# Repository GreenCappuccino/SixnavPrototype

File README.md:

# Shamrock Sixnav Prototype Board
This board is intended as a test platform for the development of an open-source knob
with 6 degrees of freedom (6DOF), based on the ideas expressed in expired US patent
[US20030102426A1](https://patents.google.com/patent/US20030102426A1).

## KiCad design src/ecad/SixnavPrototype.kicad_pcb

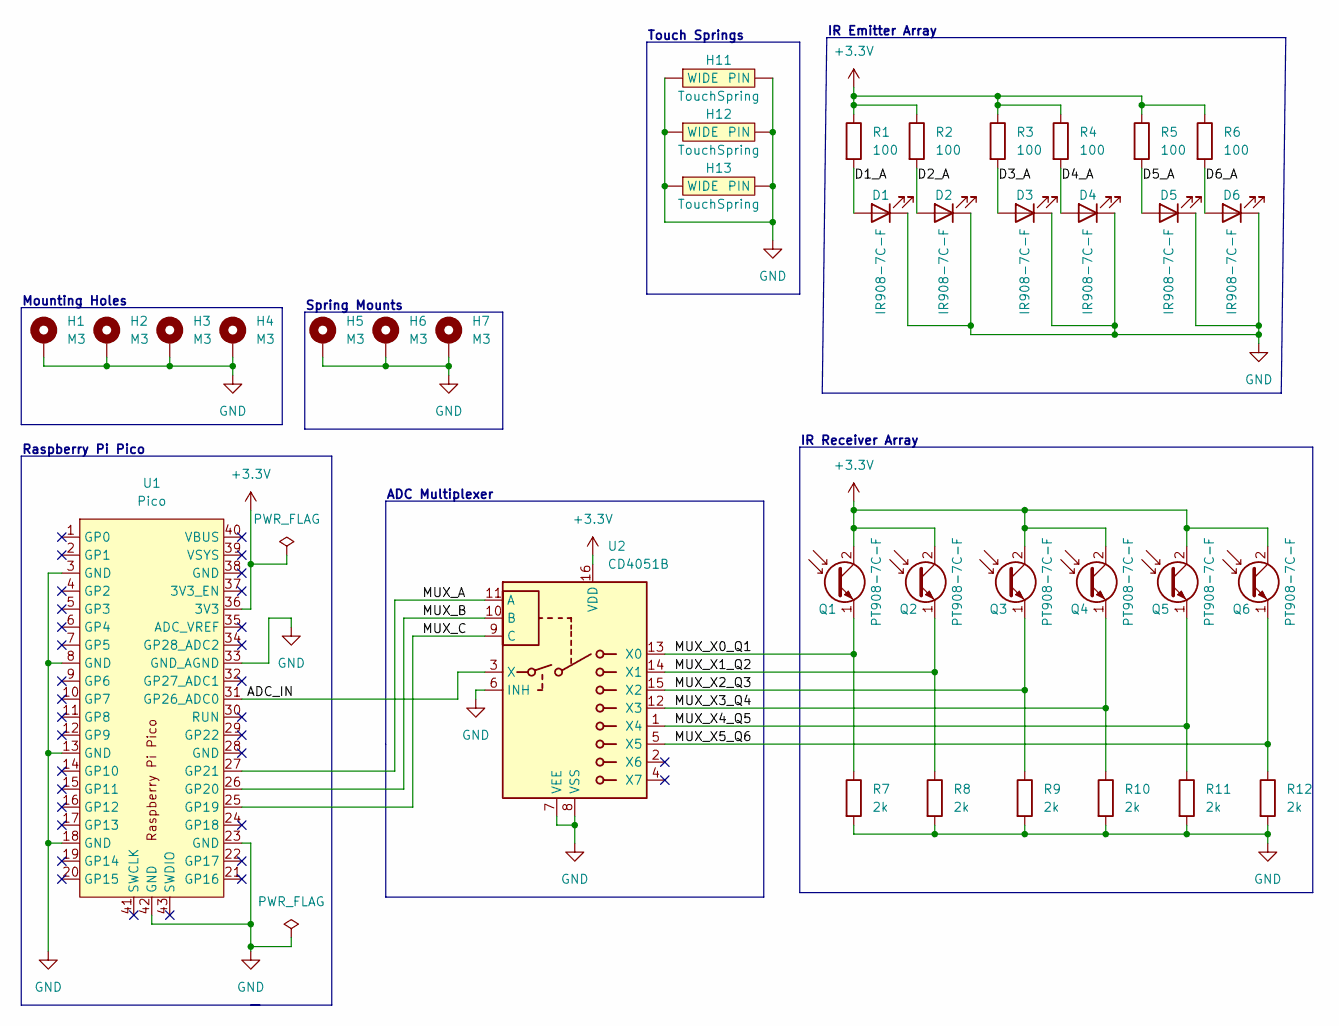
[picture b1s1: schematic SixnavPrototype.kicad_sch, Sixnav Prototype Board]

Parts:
D1, D2, D3, D4, D5, D6: IR908-7C-F
H1, H2, H3, H4, H5, H6, H7: M3; MountingHole_3.2mm_M3_DIN965_Pad
H11, H12, H13: TouchSpring; TouchSpring10mm
Q1, Q2, Q3, Q4, Q5, Q6: PT908-7C-F
R1, R2, R3, R4, R5, R6: 100; R_Axial_DIN0204_L3.6mm_D1.6mm_P5.08mm_Horizontal
R7, R8, R9, R10, R11, R12: 2k; R_Axial_DIN0204_L3.6mm_D1.6mm_P5.08mm_Horizontal
U1: Pico; Raspberry Pi Pico
U2: CD4051B; DIP-16_W7.62mm

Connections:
+3.3V: Q1.2 (C), Q2.2 (C), Q3.2 (C), Q4.2 (C), Q5.2 (C), Q6.2 (C), R1.1, R2.1, R3.1, R4.1, R5.1, R6.1, U1.36 (3V3), U2.16 (VDD)
/ADC_IN: U1.31 (GP26_ADC0), U2.3 (X)
/D1_A: D1.1 (A), R1.2
/D2_A: D2.1 (A), R2.2
/D3_A: D3.1 (A), R3.2
/D4_A: D4.1 (A), R4.2
/D5_A: D5.1 (A), R5.2
/D6_A: D6.1 (A), R6.2
/MUX_A: U1.27 (GP21), U2.11 (A)
/MUX_B: U1.26 (GP20), U2.10 (B)
/MUX_C: U1.25 (GP19), U2.9 (C)
/MUX_X0_Q1: Q1.1 (E), R7.1, U2.13 (X0)
/MUX_X1_Q2: Q2.1 (E), R8.1, U2.14 (X1)
/MUX_X2_Q3: Q3.1 (E), R9.1, U2.15 (X2)
/MUX_X3_Q4: Q4.1 (E), R10.1, U2.12 (X3)
/MUX_X4_Q5: Q5.1 (E), R11.1, U2.1 (X4)
/MUX_X5_Q6: Q6.1 (E), R12.1, U2.5 (X5)
GND: D1.2 (K), D2.2 (K), D3.2 (K), D4.2 (K), D5.2 (K), D6.2 (K), H1.1, H2.1, H3.1, H4.1, H5.1, H6.1, H7.1, H11.1 (WIDE), H11.2 (PIN), H12.1 (WIDE), H12.2 (PIN), H13.1 (WIDE), H13.2 (PIN), R7.2, R8.2, R9.2, R10.2, R11.2, R12.2, U1.3 (GND), U1.8 (GND), U1.13 (GND), U1.18 (GND), U1.23 (GND), U1.33 (GND_AGND), U1.42 (GND), U2.6 (INH), U2.7 (VEE), U2.8 (VSS)

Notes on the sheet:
Mounting Holes
ADC Multiplexer
IR Emitter Array
Touch Springs
Raspberry Pi Pico
Spring Mounts
IR Receiver Array

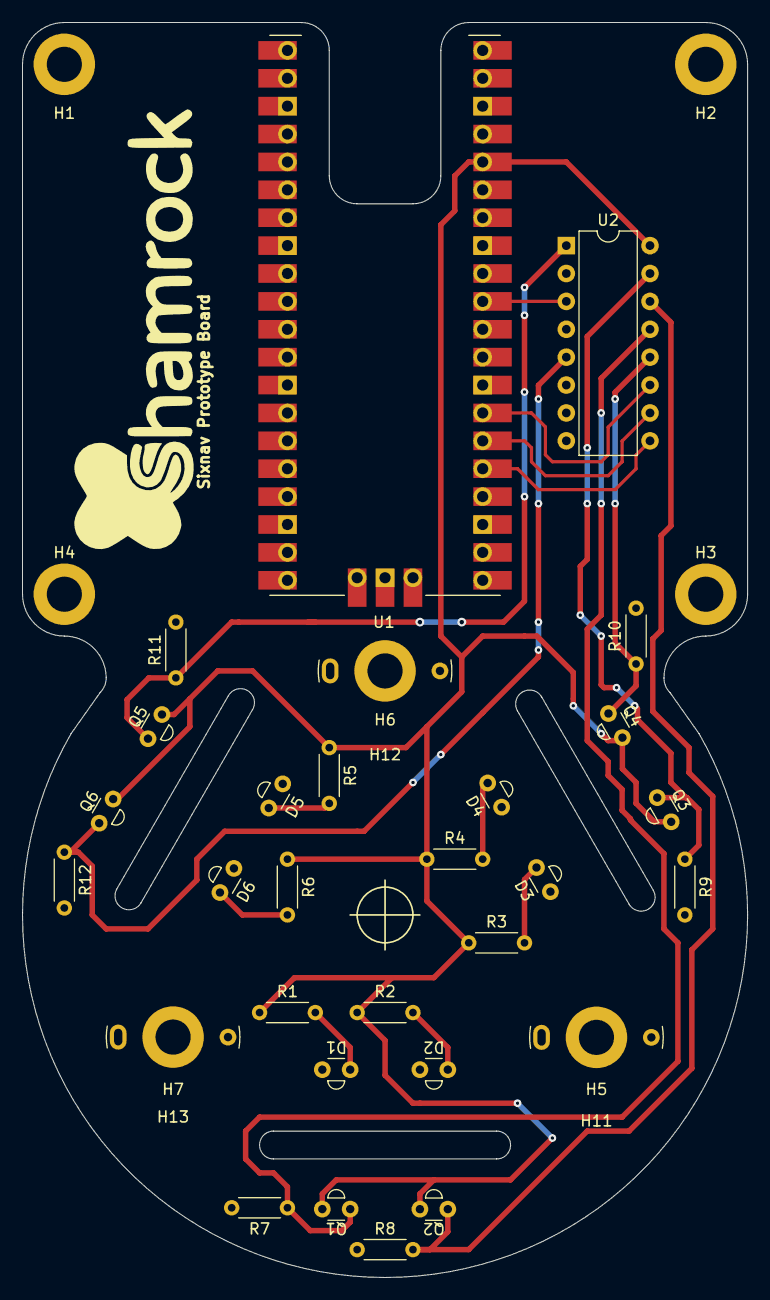
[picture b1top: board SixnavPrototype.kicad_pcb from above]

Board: 2 copper layers, 66.0 x 114.3 mm, 36 parts (0 on the bottom side), 18 nets.

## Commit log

2022-07-16 Initial Draft
2022-07-16 Second Draft
    It was only until after I finished routing this that I realized that the
    PT908 and IR908 have flipped pin numbers. I'm going to have to aquire a
    separate foorprint for the PT908.
2022-07-16 PT908 footprint
2022-07-16 First JLCPCB order
2022-07-22 Initial CI/CD
2022-07-25 Replaced symbols, footprints, models, with lib
    Internal libraries also fix the reversed phototransistor issue.
2022-07-25 ci fixes round 1
2022-07-25 ci fixes round 2
2022-07-31 fix pico castellations
2022-07-31 add symbols, fix LED polarity
2022-08-01 Add image to README
2022-08-01 add mcad STEP
2022-08-01 Create LICENSE
2022-10-04 Revision 0.2.0 ECAD
2022-10-04 Revision 0.2.0 MCAD
2022-10-04 New banner (Revision 0.2.0)
